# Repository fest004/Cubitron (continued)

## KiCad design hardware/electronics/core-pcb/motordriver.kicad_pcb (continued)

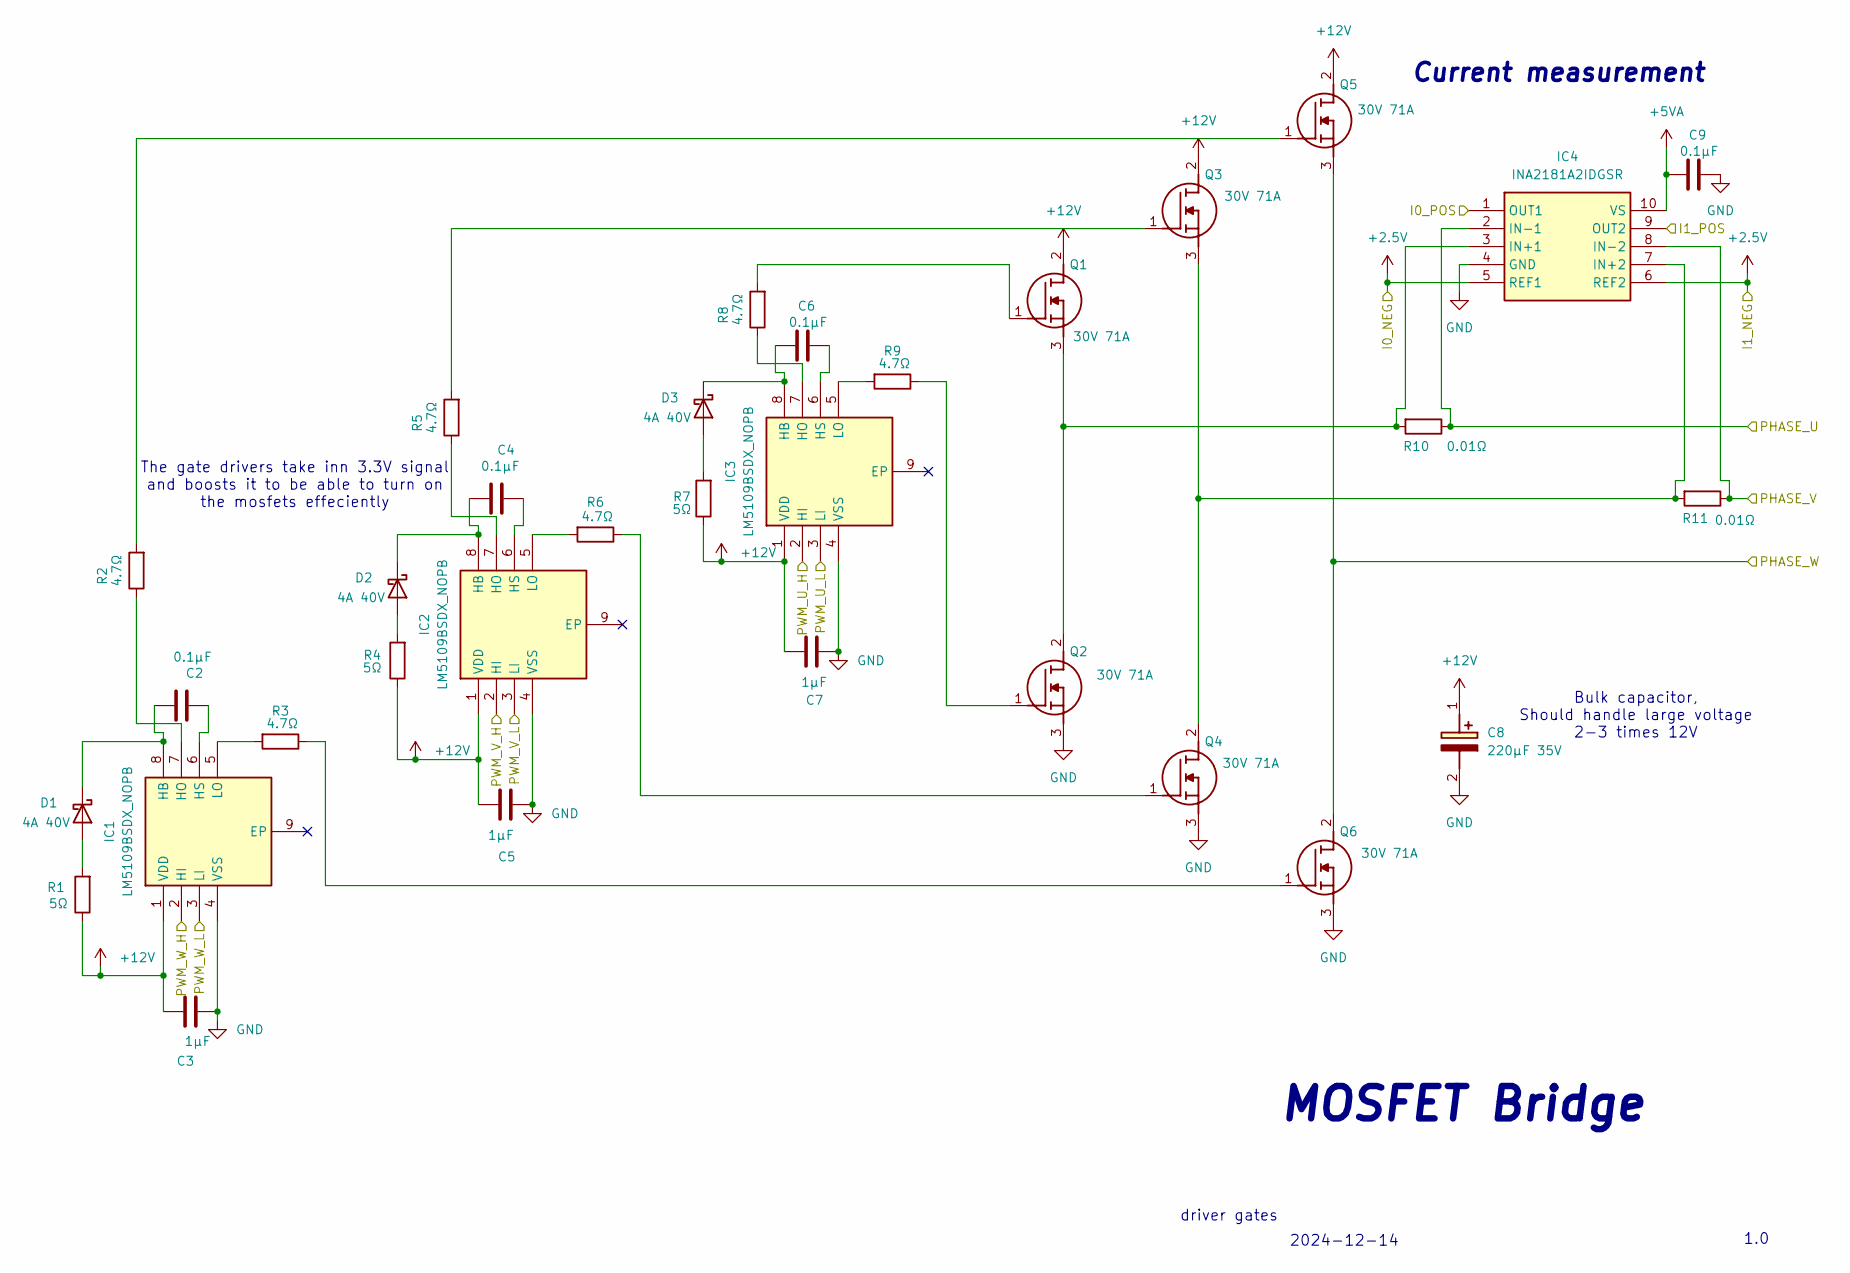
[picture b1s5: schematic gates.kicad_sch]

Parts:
C2, C4, C6, C9: 0.1µF; C_0603_1608Metric
C3, C5, C7: 1µF; C_0603_1608Metric
C8: 220µF 35V; CAPAE1050X1050N; Mouser Part Number 594-MAL215099001E3
D1, D2, D3: 4A 40V; DIOM7959X262N; Mouser Part Number 78-SL44HE3_B/I
IC1, IC2, IC3: LM5109BSDX_NOPB; SON80P400X400X80-9N; Mouser Part Number 926-LM5109BSDX/NOPB
IC4: INA2181A2IDGSR; SOP50P490X110-10N; Manufacturer_Part_Number INA2181A2IDGSR; Mouser Part Number 595-INA2181A2IDGSR
Q1, Q2, Q3, Q4, Q5, Q6: 30V 71A; IPD047N03LF2SATMA1; Manufacturer_Part_Number IPD047N03LF2SATMA1
R1, R4, R7: 5Ω; R_0603_1608Metric
R2, R3, R5, R6, R8, R9: 4.7Ω; R_0603_1608Metric
R10, R11: 0.01Ω; R_0603_1608Metric

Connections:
+2.5V: IC4.5 (REF1), IC4.6 (REF2); also elsewhere on the board
+5VA: C9.2, IC4.10 (VS); also elsewhere on the board
+12V: C3.1, C5.1, C7.1, C8.1 (+), IC1.1 (VDD), IC2.1 (VDD), IC3.1 (VDD), Q1.2 (D), Q3.2 (D), Q5.2 (D), R1.1, R4.1, R7.1; also elsewhere on the board
/gates1/PHASE_U: IC4.2 (IN-1), R10.1; also elsewhere on the board
/gates1/PHASE_V: IC4.8 (IN-2), R11.1; also elsewhere on the board
/gates1/PHASE_W: Q5.3 (S), Q6.2 (D); also elsewhere on the board
/gates1/PWM_U_H: IC3.2 (HI); also elsewhere on the board
/gates1/PWM_U_L: IC3.3 (LI); also elsewhere on the board
/gates1/PWM_V_H: IC2.2 (HI); also elsewhere on the board
/gates1/PWM_V_L: IC2.3 (LI); also elsewhere on the board
/gates1/PWM_W_H: IC1.2 (HI); also elsewhere on the board
/gates1/PWM_W_L: IC1.3 (LI); also elsewhere on the board
/servo1/ADC_I0_POS: IC4.1 (OUT1); also elsewhere on the board
/servo1/ADC_I1_POS: IC4.9 (OUT2); also elsewhere on the board
unnamed: D1.2 (A), R1.2
unnamed: C2.2, D1.1 (K), IC1.8 (HB)
unnamed: D2.2 (A), R4.2
unnamed: C4.2, D2.1 (K), IC2.8 (HB)
unnamed: D3.2 (A), R7.2
unnamed: C6.2, D3.1 (K), IC3.8 (HB)
unnamed: IC1.7 (HO), R2.1
unnamed: C2.1, IC1.6 (HS)
unnamed: IC1.5 (LO), R3.2
unnamed: IC2.7 (HO), R5.1
unnamed: C4.1, IC2.6 (HS)
unnamed: IC2.5 (LO), R6.2
unnamed: IC3.7 (HO), R8.1
unnamed: C6.1, IC3.6 (HS)
unnamed: IC3.5 (LO), R9.2
unnamed: IC4.3 (IN+1), Q1.3 (S), Q2.2 (D), R10.2
unnamed: IC4.7 (IN+2), Q3.3 (S), Q4.2 (D), R11.2
unnamed: Q1.1 (G), R8.2
unnamed: Q2.1 (G), R9.1
unnamed: Q3.1 (G), R5.2
unnamed: Q4.1 (G), R6.1
unnamed: Q5.1 (G), R2.2
unnamed: Q6.1 (G), R3.1

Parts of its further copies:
C102, C104, C106, C109, C139, C141, C143, C146: 0.1µF; C_0603_1608Metric
C103, C105, C107, C140, C142, C144: 1µF; C_0603_1608Metric
C108, C145: 220µF 35V; CAPAE1050X1050N; Mouser Part Number 594-MAL215099001E3
D51, D52, D53, D73, D74, D75: 4A 40V; DIOM7959X262N; Mouser Part Number 78-SL44HE3_B/I
IC7, IC8, IC9, IC12, IC13, IC14: LM5109BSDX_NOPB; SON80P400X400X80-9N; Mouser Part Number 926-LM5109BSDX/NOPB
IC10, IC15: INA2181A2IDGSR; SOP50P490X110-10N; Manufacturer_Part_Number INA2181A2IDGSR; Mouser Part Number 595-INA2181A2IDGSR
Q10, Q11, Q12, Q13, Q14, Q15, Q17, Q18, Q19, Q20, Q21, Q22: 30V 71A; IPD047N03LF2SATMA1; Manufacturer_Part_Number IPD047N03LF2SATMA1
R64, R67, R70, R89, R92, R95: 5Ω; R_0603_1608Metric
R65, R66, R68, R69, R71, R72, R90, R91, R93, R94, R96, R97: 4.7Ω; R_0603_1608Metric
R73, R74, R98, R99: 0.01Ω; R_0603_1608Metric

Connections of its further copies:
+2.5V: IC10.5 (REF1), IC10.6 (REF2), IC15.5 (REF1), IC15.6 (REF2); also elsewhere on the board
+5VA: C109.2, C146.2, IC10.10 (VS), IC15.10 (VS); also elsewhere on the board
+12V: C103.1, C105.1, C107.1, C108.1 (+), C140.1, C142.1, C144.1, C145.1 (+), IC7.1 (VDD), IC8.1 (VDD), IC9.1 (VDD), IC12.1 (VDD), IC13.1 (VDD), IC14.1 (VDD), Q10.2 (D), Q12.2 (D), Q14.2 (D), Q17.2 (D), Q19.2 (D), Q21.2 (D), R64.1, R67.1, R70.1, R89.1, R92.1, R95.1; also elsewhere on the board
/gates2/PHASE_U: IC10.2 (IN-1), R73.1; also elsewhere on the board
/gates2/PHASE_V: IC10.8 (IN-2), R74.1; also elsewhere on the board
/gates2/PHASE_W: Q14.3 (S), Q15.2 (D); also elsewhere on the board
/gates2/PWM_U_H: IC9.2 (HI); also elsewhere on the board
/gates2/PWM_U_L: IC9.3 (LI); also elsewhere on the board
/gates2/PWM_V_H: IC8.2 (HI); also elsewhere on the board
/gates2/PWM_V_L: IC8.3 (LI); also elsewhere on the board
/gates2/PWM_W_H: IC7.2 (HI); also elsewhere on the board
/gates2/PWM_W_L: IC7.3 (LI); also elsewhere on the board
/gates3/PHASE_U: IC15.2 (IN-1), R98.1; also elsewhere on the board
/gates3/PHASE_V: IC15.8 (IN-2), R99.1; also elsewhere on the board
/gates3/PHASE_W: Q21.3 (S), Q22.2 (D); also elsewhere on the board
/gates3/PWM_U_H: IC14.2 (HI); also elsewhere on the board
/gates3/PWM_U_L: IC14.3 (LI); also elsewhere on the board
/gates3/PWM_V_H: IC13.2 (HI); also elsewhere on the board
/gates3/PWM_V_L: IC13.3 (LI); also elsewhere on the board
/gates3/PWM_W_H: IC12.2 (HI); also elsewhere on the board
/gates3/PWM_W_L: IC12.3 (LI); also elsewhere on the board
/servo2/ADC_I0_POS: IC10.1 (OUT1); also elsewhere on the board
/servo2/ADC_I1_POS: IC10.9 (OUT2); also elsewhere on the board
/servo3/ADC_I0_POS: IC15.1 (OUT1); also elsewhere on the board
/servo3/ADC_I1_POS: IC15.9 (OUT2); also elsewhere on the board
unnamed: D51.2 (A), R64.2
unnamed: C102.2, D51.1 (K), IC7.8 (HB)
unnamed: D52.2 (A), R67.2
unnamed: C104.2, D52.1 (K), IC8.8 (HB)
unnamed: D53.2 (A), R70.2
unnamed: C106.2, D53.1 (K), IC9.8 (HB)
unnamed: D73.2 (A), R89.2
unnamed: C139.2, D73.1 (K), IC12.8 (HB)
unnamed: D74.2 (A), R92.2
unnamed: C141.2, D74.1 (K), IC13.8 (HB)
unnamed: D75.2 (A), R95.2
unnamed: C143.2, D75.1 (K), IC14.8 (HB)
unnamed: IC7.7 (HO), R65.1
unnamed: C102.1, IC7.6 (HS)
unnamed: IC7.5 (LO), R66.2
unnamed: IC8.7 (HO), R68.1
unnamed: C104.1, IC8.6 (HS)
unnamed: IC8.5 (LO), R69.2
unnamed: IC9.7 (HO), R71.1
unnamed: C106.1, IC9.6 (HS)
unnamed: IC9.5 (LO), R72.2
unnamed 173: IC10.3 (IN+1), Q10.3 (S), Q11.2 (D), R73.2; also elsewhere on the board
unnamed 174: IC10.7 (IN+2), Q12.3 (S), Q13.2 (D), R74.2; also elsewhere on the board
unnamed: IC12.7 (HO), R90.1
unnamed: C139.1, IC12.6 (HS)
unnamed: IC12.5 (LO), R91.2
unnamed: IC13.7 (HO), R93.1
unnamed: C141.1, IC13.6 (HS)
unnamed: IC13.5 (LO), R94.2
unnamed: IC14.7 (HO), R96.1
unnamed: C143.1, IC14.6 (HS)
unnamed: IC14.5 (LO), R97.2
unnamed: IC15.3 (IN+1), Q17.3 (S), Q18.2 (D), R98.2
unnamed: IC15.7 (IN+2), Q19.3 (S), Q20.2 (D), R99.2
unnamed 198: Q10.1 (G), R71.2; also elsewhere on the board
unnamed 199: Q11.1 (G), R72.1; also elsewhere on the board
unnamed 200: Q12.1 (G), R68.2; also elsewhere on the board
unnamed 201: Q13.1 (G), R69.1; also elsewhere on the board
unnamed: Q14.1 (G), R65.2
unnamed: Q15.1 (G), R66.1
unnamed: Q17.1 (G), R96.2
unnamed: Q18.1 (G), R97.1
unnamed: Q19.1 (G), R93.2
unnamed: Q20.1 (G), R94.1
unnamed: Q21.1 (G), R90.2
unnamed: Q22.1 (G), R91.1

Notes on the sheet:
1.0
The gate drivers take inn 3.3V signal and boosts it to be able to turn on the mosfets effeciently
MOSFET Bridge
driver gates
2024-12-14
Current measurement
Bulk capacitor, Should handle large voltage 2-3 times 12V

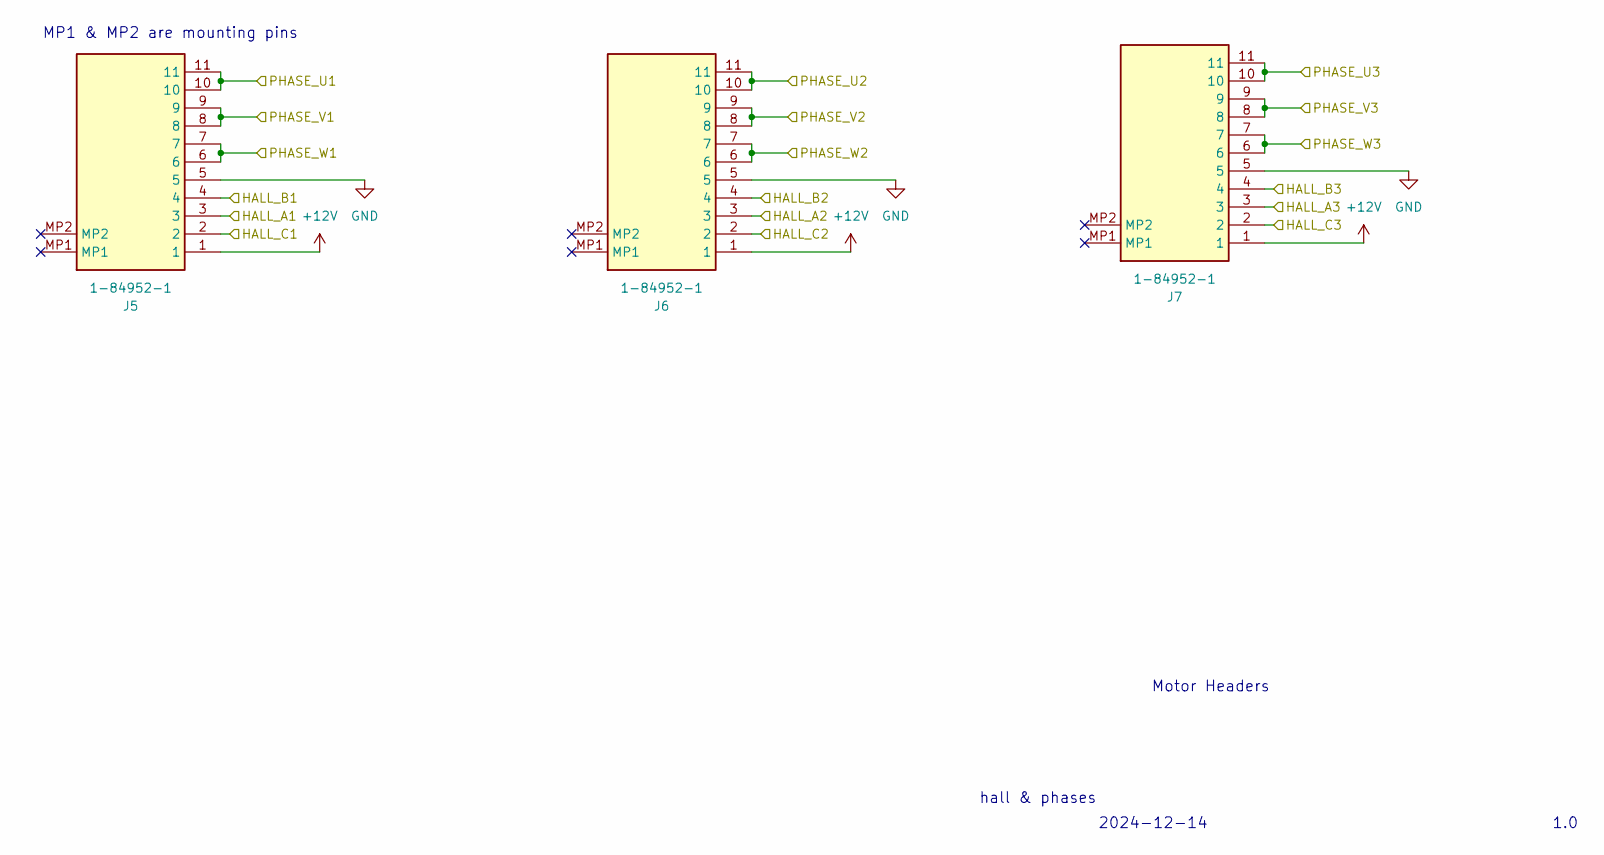
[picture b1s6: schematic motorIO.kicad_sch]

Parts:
J5, J6, J7: 1-84952-1; 1849521; Mouser Part Number 571-1-84952-1

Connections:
+12V: J5.1, J6.1, J7.1; also elsewhere on the board
/gates1/PHASE_U: J7.10, J7.11; also elsewhere on the board
/gates1/PHASE_V: J7.8, J7.9; also elsewhere on the board
/gates1/PHASE_W: J7.6, J7.7; also elsewhere on the board
/gates2/PHASE_U: J6.10, J6.11; also elsewhere on the board
/gates2/PHASE_V: J6.8, J6.9; also elsewhere on the board
/gates2/PHASE_W: J6.6, J6.7; also elsewhere on the board
/gates3/PHASE_U: J5.10, J5.11; also elsewhere on the board
/gates3/PHASE_V: J5.8, J5.9; also elsewhere on the board
/gates3/PHASE_W: J5.6, J5.7; also elsewhere on the board
/motorIO/HALL_A1: J5.3; also elsewhere on the board
/motorIO/HALL_A2: J6.3; also elsewhere on the board
/motorIO/HALL_A3: J7.3; also elsewhere on the board
/motorIO/HALL_B1: J5.4; also elsewhere on the board
/motorIO/HALL_B2: J6.4; also elsewhere on the board
/motorIO/HALL_B3: J7.4; also elsewhere on the board
/motorIO/HALL_C1: J5.2; also elsewhere on the board
/motorIO/HALL_C2: J6.2; also elsewhere on the board
/motorIO/HALL_C3: J7.2; also elsewhere on the board

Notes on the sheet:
1.0
MP1 & MP2 are mounting pins
Motor Headers
2024-12-14
hall & phases

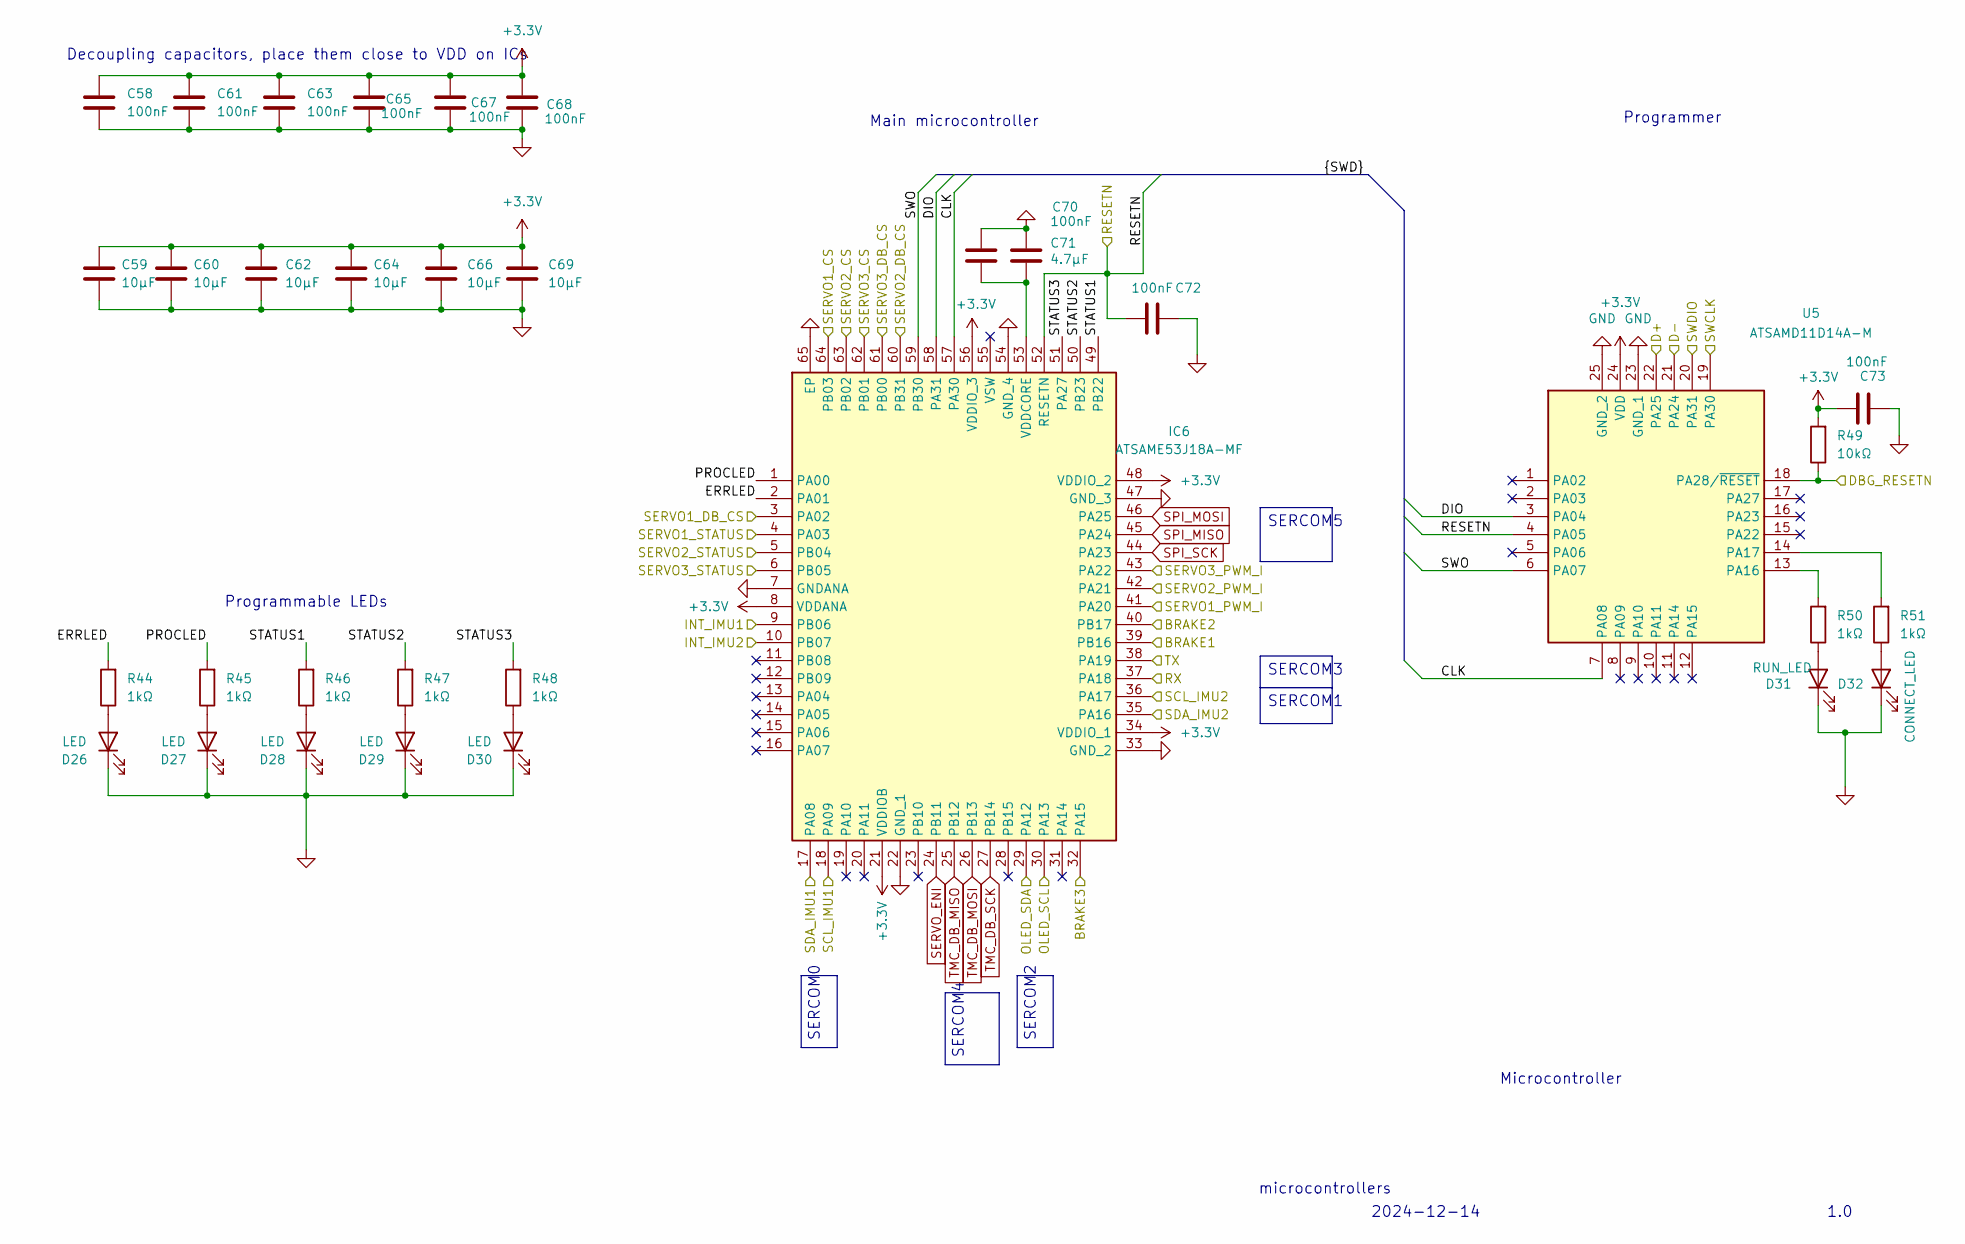
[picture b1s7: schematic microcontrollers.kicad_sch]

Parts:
C58, C61, C63, C65, C67, C68, C70, C72, C73: 100nF; C_0603_1608Metric
C59, C60, C62, C64, C66, C69: 10µF; C_0603_1608Metric
C71: 4.7µF; C_0603_1608Metric
D26, D27, D28, D29, D30: LED; D_0603_1608Metric
D31: RUN_LED; D_0603_1608Metric
D32: CONNECT_LED; D_0603_1608Metric
IC6: ATSAME53J18A-MF; QFN50P900X900X100-65N-D; Manufacturer_Part_Number ATSAME53J18A-MF; Mouser Part Number 556-ATSAME53J18A-MF
R44, R45, R46, R47, R48, R50, R51: 1kΩ; R_0603_1608Metric
R49: 10kΩ; R_0603_1608Metric
U5: ATSAMD11D14A-M; QFN50P400X400X90-25N-D; Mouser Part Number 556-ATSAMD11D14A-MNT

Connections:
+3.3V: C58.1, C59.1, C60.1, C61.1, C62.1, C63.1, C64.1, C65.1, C66.1, C67.1, C68.1, C69.1, C73.1, IC6.8 (VDDANA), IC6.21 (VDDIOB), IC6.34 (VDDIO_1), IC6.48 (VDDIO_2), IC6.56 (VDDIO_3), R49.2, U5.24 (VDD); also elsewhere on the board
/IO/BRAKE1: IC6.39 (PB16); also elsewhere on the board
/IO/BRAKE2: IC6.40 (PB17); also elsewhere on the board
/IO/BRAKE3: IC6.32 (PA15); also elsewhere on the board
/IO/D+: U5.22 (PA25); also elsewhere on the board
/IO/D-: U5.21 (PA24); also elsewhere on the board
/IO/DBG_RESETN: R49.1, U5.18 (PA28/~RESET); also elsewhere on the board
/IO/DBG_SWCLK: U5.19 (PA30); also elsewhere on the board
/IO/DBG_SWDIO: U5.20 (PA31); also elsewhere on the board
/IO/INT_IMU1: IC6.9 (PB06); also elsewhere on the board
/IO/INT_IMU2: IC6.10 (PB07); also elsewhere on the board
/IO/OLED_SCL: IC6.30 (PA13); also elsewhere on the board
/IO/OLED_SDA: IC6.29 (PA12); also elsewhere on the board
/IO/RX: IC6.37 (PA18); also elsewhere on the board
/IO/SCL_IMU1: IC6.18 (PA09); also elsewhere on the board
/IO/SCL_IMU2: IC6.36 (PA17); also elsewhere on the board
/IO/SDA_IMU1: IC6.17 (PA08); also elsewhere on the board
/IO/SDA_IMU2: IC6.35 (PA16); also elsewhere on the board
/IO/TX: IC6.38 (PA19); also elsewhere on the board
/microcontrollers/CLK: IC6.57 (PA30), U5.7 (PA08)
/microcontrollers/DIO: IC6.58 (PA31), U5.3 (PA04)
/microcontrollers/ERRLED: IC6.2 (PA01), R44.2; also elsewhere on the board
/microcontrollers/PROCLED: IC6.1 (PA00), R45.2; also elsewhere on the board
/microcontrollers/RESETN: C72.1, IC6.52 (RESETN), U5.4 (PA05); also elsewhere on the board
/microcontrollers/SERVO1_CS: IC6.64 (PB03); also elsewhere on the board
/microcontrollers/SERVO1_DB_CS: IC6.3 (PA02); also elsewhere on the board
/microcontrollers/SERVO1_PWM_I: IC6.41 (PA20); also elsewhere on the board
/microcontrollers/SERVO1_STATUS: IC6.4 (PA03); also elsewhere on the board
/microcontrollers/SERVO2_CS: IC6.63 (PB02); also elsewhere on the board
/microcontrollers/SERVO2_DB_CS: IC6.60 (PB31); also elsewhere on the board
/microcontrollers/SERVO2_PWM_I: IC6.42 (PA21); also elsewhere on the board
/microcontrollers/SERVO2_STATUS: IC6.5 (PB04); also elsewhere on the board
/microcontrollers/SERVO3_CS: IC6.62 (PB01); also elsewhere on the board
/microcontrollers/SERVO3_DB_CS: IC6.61 (PB00); also elsewhere on the board
/microcontrollers/SERVO3_PWM_I: IC6.43 (PA22); also elsewhere on the board
/microcontrollers/SERVO3_STATUS: IC6.6 (PB05); also elsewhere on the board
/microcontrollers/STATUS1: IC6.49 (PB22), R46.2
/microcontrollers/STATUS2: IC6.50 (PB23), R47.2
/microcontrollers/STATUS3: IC6.51 (PA27), R48.2
/microcontrollers/SWO: IC6.59 (PB30), U5.6 (PA07)
unnamed: D26.2 (A), R44.1
unnamed: D27.2 (A), R45.1
unnamed: D28.2 (A), R46.1
unnamed: D29.2 (A), R47.1
unnamed: D30.2 (A), R48.1
unnamed: D31.2 (A), R50.1
unnamed: D32.2 (A), R51.1
unnamed: C70.2, C71.2, IC6.53 (VDDCORE)
unnamed: R50.2, U5.13 (PA16)
unnamed: R51.2, U5.14 (PA17)
SERVO_ENI: IC6.24 (PB11); also elsewhere on the board
SPI_MISO: IC6.45 (PA24); also elsewhere on the board
SPI_MOSI: IC6.46 (PA25); also elsewhere on the board
SPI_SCK: IC6.44 (PA23); also elsewhere on the board
TMC_DB_MISO: IC6.25 (PB12); also elsewhere on the board
TMC_DB_MOSI: IC6.26 (PB13); also elsewhere on the board
TMC_DB_SCK: IC6.27 (PB14); also elsewhere on the board

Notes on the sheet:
Main microcontroller
1.0
microcontrollers
Programmable LEDs
Microcontroller
2024-12-14
Programmer
Decoupling capacitors, place them close to VDD on ICs
SERCOM0
SERCOM4
SERCOM5
SERCOM1
SERCOM2
SERCOM3

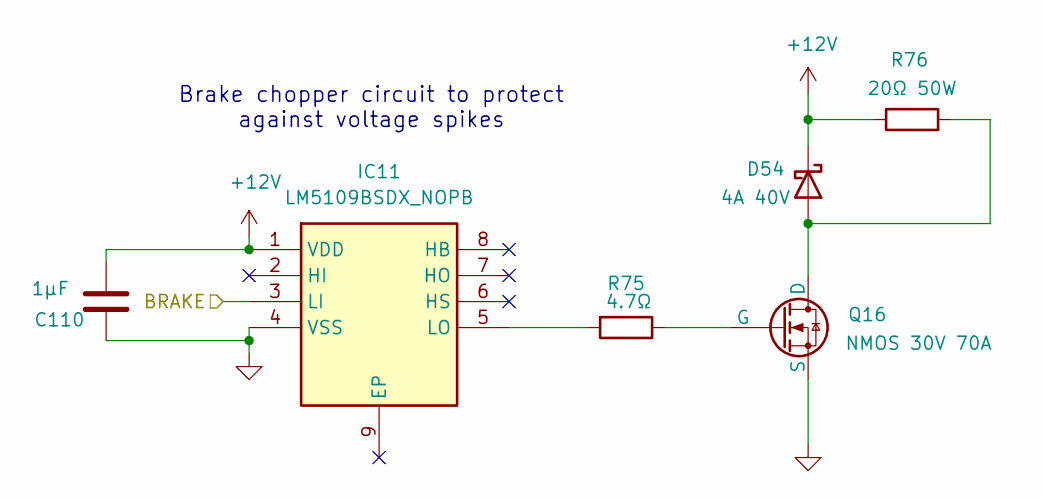
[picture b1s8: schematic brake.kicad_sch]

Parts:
C110: 1µF; C_0603_1608Metric
D54: 4A 40V; DIOM7959X262N; Mouser Part Number 78-SL44HE3_B/I
IC11: LM5109BSDX_NOPB; SON80P400X400X80-9N; Mouser Part Number 926-LM5109BSDX/NOPB
Q16: NMOS 30V 70A; IPD047N03LF2SATMA1
R75: 4.7Ω; R_0603_1608Metric
R76: 20Ω 50W

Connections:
+12V: C110.1, D54.1 (K), IC11.1 (VDD), R76.1; also elsewhere on the board
/brake/BRAKE: IC11.3 (LI); also elsewhere on the board
unnamed: D54.2 (A), Q16.1 (D), R76.2
unnamed: IC11.5 (LO), R75.2
unnamed: Q16.2 (G), R75.1

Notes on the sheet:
Brake chopper circuit to protect against voltage spikes

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
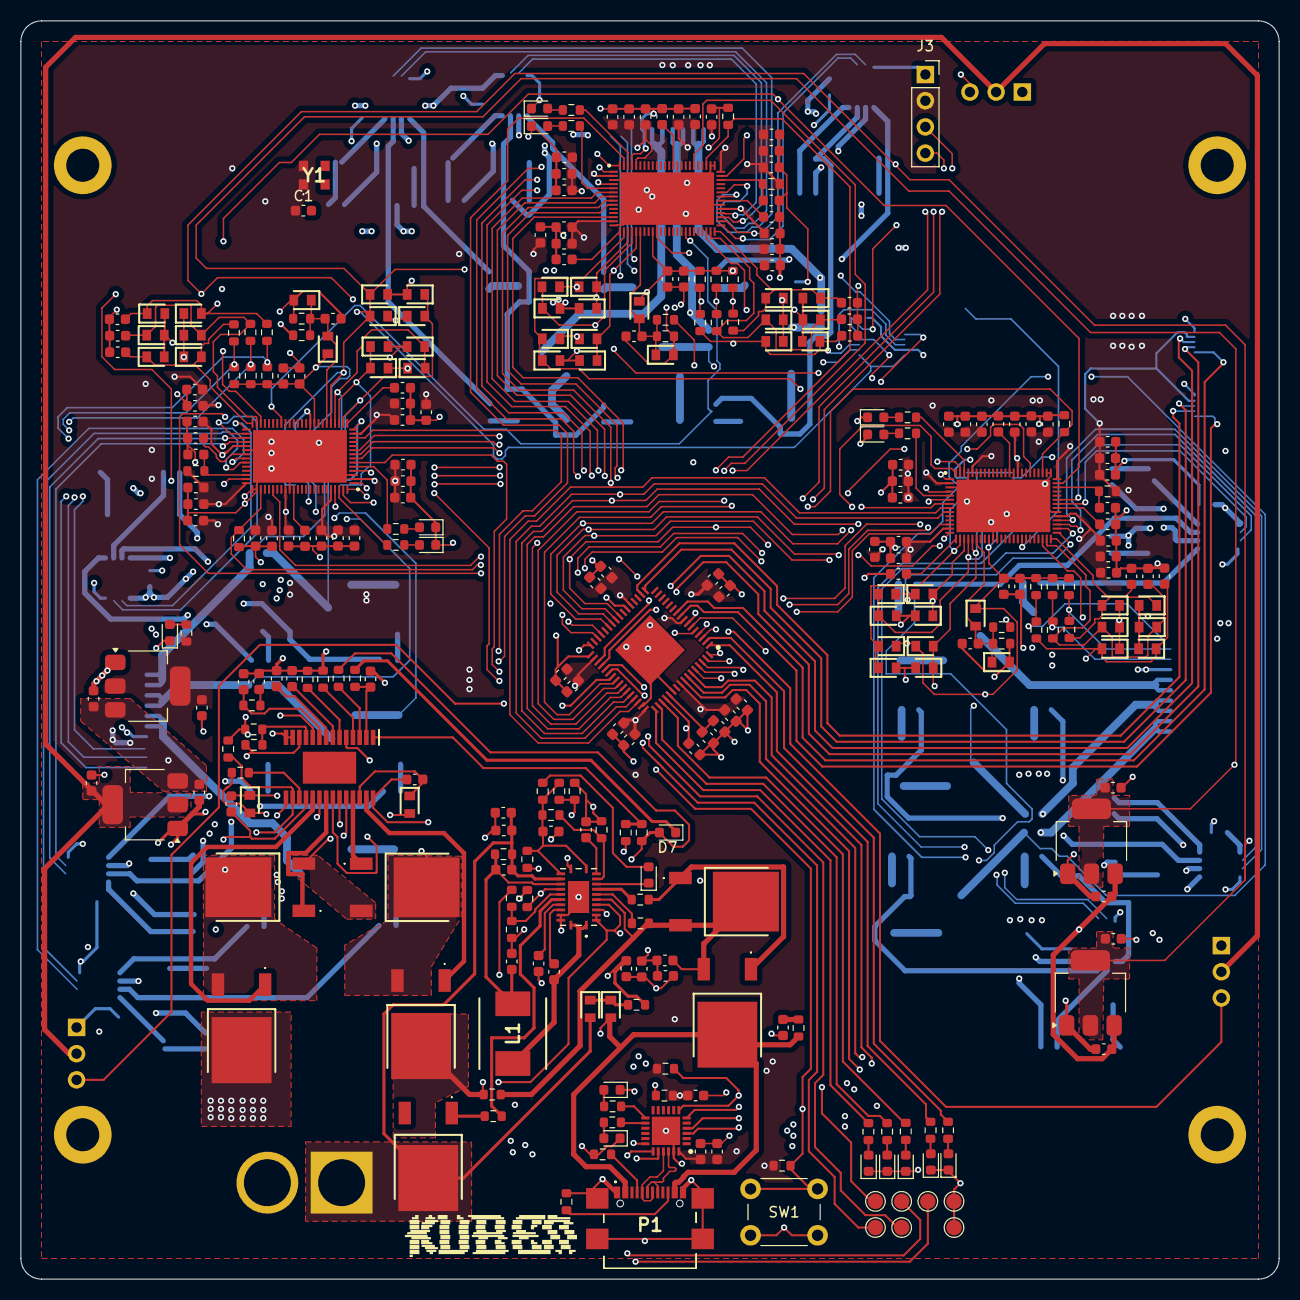
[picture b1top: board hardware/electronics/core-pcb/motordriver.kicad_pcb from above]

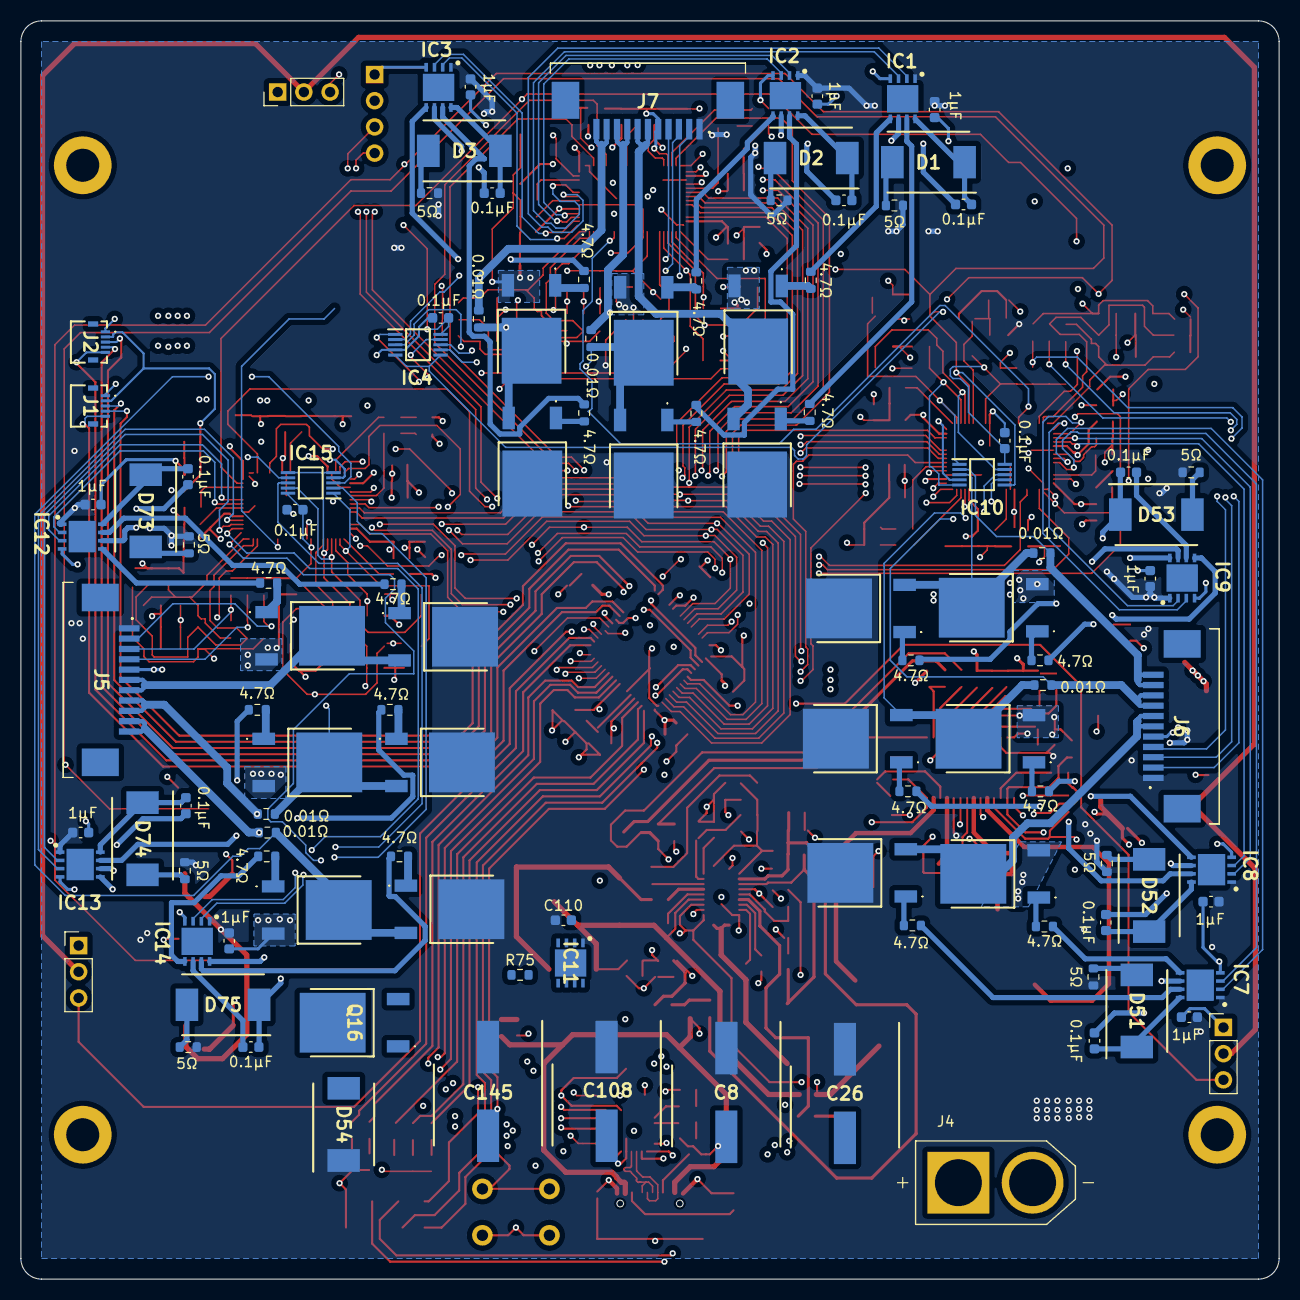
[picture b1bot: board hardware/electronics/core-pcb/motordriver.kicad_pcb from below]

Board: 4 copper layers, 122.0 x 122.0 mm, 418 parts (111 on the bottom side), 241 nets.

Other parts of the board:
C22#2: 10µF; C_0603_1608Metric
C26#2: 220µF 35V; CAPAE1050X1050N
C30#2, C32#2, C33#2, C35#2, C36#2: 100nF; C_0603_1608Metric
C34#2, C37#2: 100pF; C_0603_1608Metric
D7#2: PWR; D_0603_1608Metric
D9#2, D10#2: 4.7Vf 0.5A; DIOC1709X85N
IC6#2: ATSAME53J18A-MF; SOP65P640X120-29N
Q10#2, Q11#2, Q12#2, Q13#2: 30V 71A; IPD047N03LF2SATMA1
R28#2, R35#2, R36#2, R37#2, R39#2: 1kΩ; R_0603_1608Metric
R30#2: 5.1kΩ; R_0603_1608Metric
R31#2, R38#2, R60#2: 10kΩ; R_0603_1608Metric
R32#2, R33#2, R34#2: 4.7kΩ; R_0603_1608Metric
U3#2: LD1117S25TR_SOT223; SOT-223-3_TabPin2

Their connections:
+2.5V: U3#2.2 (VO); also elsewhere on the board
+3.3V: C30#2.2, C32#2.2, C33#2.2, C35#2.2, IC6#2.8 (VDDANA), IC6#2.21 (VDDIOB), R28#2.2, R31#2.1, R60#2.2; also elsewhere on the board
+5VA: D10#2.1 (K), R32#2.1, R33#2.1, R34#2.1; also elsewhere on the board
+12V: C26#2.1 (+), Q10#2.2 (D), Q12#2.2 (D), U3#2.3 (VI); also elsewhere on the board
/IO/INT_IMU1: IC6#2.9 (PB06); also elsewhere on the board
/IO/INT_IMU2: IC6#2.10 (PB07); also elsewhere on the board
/IO/OLED_SDA: IC6#2.29 (PA12); also elsewhere on the board
/IO/SCL_IMU1: IC6#2.18 (PA09); also elsewhere on the board
/IO/SDA_IMU1: IC6#2.17 (PA08); also elsewhere on the board
/microcontrollers/ERRLED: IC6#2.2 (PA01); also elsewhere on the board
/microcontrollers/PROCLED: IC6#2.1 (PA00); also elsewhere on the board
/microcontrollers/RESETN: R31#2.2; also elsewhere on the board
/microcontrollers/SERVO1_DB_CS: IC6#2.3 (PA02); also elsewhere on the board
/microcontrollers/SERVO1_STATUS: IC6#2.4 (PA03); also elsewhere on the board
/microcontrollers/SERVO2_STATUS: IC6#2.5 (PB04); also elsewhere on the board
/microcontrollers/SERVO3_STATUS: IC6#2.6 (PB05); also elsewhere on the board
/motorIO/HALL_A3: R32#2.2, R37#2.1; also elsewhere on the board
/motorIO/HALL_B3: R33#2.2, R36#2.1; also elsewhere on the board
/motorIO/HALL_C3: R34#2.2, R35#2.1; also elsewhere on the board
/servo1/ADC_I0_POS: D9#2.1 (K); also elsewhere on the board
/servo1/ADC_I1_POS: D10#2.2 (A); also elsewhere on the board
/servo1/HALL_U_FILT: C34#2.2, R37#2.2; also elsewhere on the board
/servo1/HALL_V_FILT: C37#2.2, R36#2.2; also elsewhere on the board
/servo1/HALL_W_FILT: R35#2.2; also elsewhere on the board
BATTERY_P: C22#2.1; also elsewhere on the board
unnamed 111: D7#2.2 (A), R28#2.1; also elsewhere on the board
unnamed 112: R39#2.1; also elsewhere on the board
unnamed 173: Q10#2.3 (S), Q11#2.2 (D); also elsewhere on the board
unnamed 174: Q12#2.3 (S), Q13#2.2 (D); also elsewhere on the board
unnamed 188: R30#2.2; also elsewhere on the board
unnamed 198: Q10#2.1 (G); also elsewhere on the board
unnamed 199: Q11#2.1 (G); also elsewhere on the board
unnamed 200: Q12#2.1 (G); also elsewhere on the board
unnamed 201: Q13#2.1 (G); also elsewhere on the board
unnamed 211: R39#2.2; also elsewhere on the board
unnamed 216: C36#2.2; also elsewhere on the board
unnamed 221: R60#2.1; also elsewhere on the board
SERVO_ENI: IC6#2.24 (PB11), R38#2.1; also elsewhere on the board
TMC_DB_MISO: IC6#2.25 (PB12); also elsewhere on the board
TMC_DB_MOSI: IC6#2.26 (PB13); also elsewhere on the board
TMC_DB_SCK: IC6#2.27 (PB14); also elsewhere on the board
